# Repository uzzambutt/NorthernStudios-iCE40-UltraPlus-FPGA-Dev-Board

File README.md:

# NorthernStudios iCE40-UltraPlus FPGA Dev Board (V2)

<p align="center">
  <b>Designed by: Muhammad Uzzam Butt</b>
</p>

<p align="center">

</p>

---

## Overview
**NorthernStudios iCE40-UltraPlus FPGA Dev Board (V2)** is a small, open-source development board based on the tiny form factor that utilizes **Lattice iCE40 UltraPlus (iCE40UP5K)** FPGA. This development board is specially built for low power edge computing, TinyML, RISC-V softcores and hardware developments.

The features of this development board include the integrated USB-to-UART bridge, 128M-bit SPI Flash and the multi rail power supply system.

---

##  Hardware Specifications

### FPGA Chip: Lattice iCE40UP5K
* **Logic Cells**: 5,280 Look-Up Tables (LUTs)
* **Block RAM (BRAM)**: 120 Kbit
* **Single-Port RAM (SPRAM)**: 1,024 Kbit (128 KB, ideal for microcontroller program memory)
* **DSP Blocks**: 8 (16x16 multiplier + 32-bit accumulator)
* **Hardened IP**: 2x I2C, 2x SPI
* **Constant Current Drivers**: 3x 24mA dedicated driver outputs (suited for RGB LED control)

### Important components
| Component | Function | Description |
| :--- | :--- | :--- |
| **FPGA** | [Lattice iCE40UP5K-SG48ITR](https://www.latticesemi.com/Products/FPGAandCPLD/iCE40UltraPlus) | SG48 package, 48-pin QFN, highly integrated low-power FPGA. |
| **USB-to-UART Bridge** | [Silicon Labs CP2102N](https://www.silabs.com/interface/usb-bridges/usbtouart/device.cp2102n-a02-gqfn24) | High-speed USB-to-UART bridge for programming and serial debugging via USB-C. |
| **SPI Flash** | Winbond W25Q128JVS (128M-bit / 16MB) | Stores FPGA configuration bitstreams and extra user data or filesystem blocks. |
| **Reference Oscillator** | Seiko Epson SG-210STF (12 MHz) | Ultra-precise active crystal oscillator providing a stable system reference clock. |
| **Power Regulators** | Diodes Inc. AP2112K LDOs | Generates +1.2V (Core), +1.8V (PLL/VCC), +2.5V (Auxiliary), and +3.3V (I/O & Flash) from USB +5V. |
| **USB Connector** | USB Type-C Receptacle (14-Pin) | Handles 5V power supply, programming interface, and UART communications. |

---

##  Onboard Interfaces & I/O
* **RGB LED**: Dedicated addressable RGB LED (LED_ARGB) connected to the FPGA's constant current outputs for status and visualization.
* **User I/O**: Multi-pin expansion breakout headers featuring standard 0.1" pitch GPIO pins.
* **Tactile Buttons**:
  * Reset Button
  * User Programmable Button

---

## PCB Design & Layers

This PCB is designed as a high-density, **4-layer board** utilizing KiCad to ensure clean signal routing, stable ground planes, and dedicated power rails. 

###  Outer Silkscreen & Soldermask
* **Front View (Main Thumbnail)**:
  
* **Back View**:

###  Internal Copper Layers
* **Layer 1 (L1 - Top Copper / Signals)**:
  
* **Layer 2 (L2 - Inner Ground Plane)**:
  
* **Layer 3 (L3 - Inner Power Plane)**:
  
* **Layer 4 (L4 - Bottom Copper / Signals)**:

---

## Bill of Materials (BOM)

The complete bill of materials for the board is listed below. You can also view the raw CSV file [bom.csv](file:///D:/NS%20FPGA%20V2/NS%20FPGA%20V2%20iCE/jlcpcb/production_files/bom.csv).

| Comment | Designator | Footprint | LCSC | Quantity |
| :--- | :--- | :--- | :--- | :--- |
| 0.1uF | C10,C11,C14,C18,C19,C20,C21,C22,C23,C24,C26 | C_0402_1005Metric | C141382 | 11 |
| 1.5k | R12,R13,R14,R17 | R_0402_1005Metric | C25867 | 4 |
| 100 | R8 | R_0603_1608Metric | C22775 | 1 |
| 100nF | C15,C17 | C_0402_1005Metric | C1525 | 2 |
| 10k | R10,R11,R15,R16,R6,R7 | R_0402_1005Metric | C25531 | 6 |
| 10uF | C16 | C_0402_1005Metric | C15525 | 1 |
| 10uF | C1,C2,C3,C4,C5,C6,C7,C8 | C_0603_1608Metric | C19702 | 8 |
| 1k | R1 | R_0402_1005Metric | C25543 | 1 |
| 1uF | C25 | C_0402_1005Metric | C52923 | 1 |
| 22.1k | R5 | R_0402_1005Metric | C43473 | 1 |
| 4.7uF | C12,C13,C9 | C_0402_1005Metric | C23733 | 3 |
| 47.5k | R4 | R_0402_1005Metric | C137974 | 1 |
| 5.1k | R2,R3 | R_0603_1608Metric | C23186 | 2 |
| AP2112K-1.2 | U5 | SOT-23-5 | C460310 | 1 |
| AP2112K-1.8 | U7 | SOT-23-5 | C3021123 | 1 |
| AP2112K-2.5 | U6 | SOT-23-5 | C49451993 | 1 |
| AP2112K-3.3 | U4 | SOT-23-5 | C51118 | 1 |
| CP2102N-Axx-xQFN24 | U3 | QFN-24-1EP_4x4mm_P0.5mm_EP2.6x2.6mm | C969151 | 1 |
| D_Schottky | D1 | D_0603_1608Metric | C6770543 | 1 |
| ICE40UP5K-SG48ITR | U1 | QFN-48-1EP_7x7mm_P0.5mm_EP5.1x5.1mm | C2678152 | 1 |
| LED | D2,D4 | LED_0402_1005Metric | C130723 | 2 |
| LED_ARGB | D3 | LED_RGB_Wuerth-PLCC4_3.2x2.8mm_150141M173100 | C7288905 | 1 |
| R22 | R9 | R_0402_1005Metric | C25092 | 1 |
| SG-210STF | Y1 | Oscillator_SMD_SeikoEpson_SG210-4Pin_2.5x2.0mm | C728996 | 1 |
| SW_Push | SW1 | SW_Push_1P1T_NO_CK_KMR2 | C221679 | 1 |
| USB_C_Receptacle_USB2.0_14P | J1 | USB_C_Receptacle_HRO_TYPE-C-31-M-12 | C2894897 | 1 |
| W25Q128JVS | U2 | SOIC-8_5.3x5.3mm_P1.27mm | C97521 | 1 |
| Conn_02x03_Odd_Even | J5 | PinHeader_2x03_P1.00mm_Vertical | | 1 |
| Conn_02x03_Odd_Even | J4 | PinHeader_2x03_P1.00mm_Vertical | | 1 |
| TestPoint_Small | TP4 | TestPoint_Pad_D1.0mm | | 1 |
| TestPoint_Small | TP3 | TestPoint_Pad_D1.0mm | | 1 |
| TestPoint_Small | TP2 | TestPoint_Pad_D1.0mm | | 1 |
| TestPoint_Small | TP1 | TestPoint_Pad_D1.0mm | | 1 |
| Conn_01x07_Pin | J6 | PinHeader_1x07_P2.54mm_Vertical | | 1 |
| Conn_01x20_Pin | J3 | PinHeader_1x20_P2.54mm_Vertical | | 1 |
| Conn_01x20_Pin | J2 | PinHeader_1x20_P2.54mm_Vertical | | 1 |

---

## Getting Started

### 💻 Open Source Toolchain Setup
The Lattice iCE40 UltraPlus is fully supported by the open-source FPGA toolchain, providing quick compilation and programming:

1. **Synthesis**: [Yosys](https://github.com/YosysHQ/yosys)
2. **Place & Route**: [nextpnr](https://github.com/YosysHQ/nextpnr) (using target `--up5k`)
3. **Bitstream Packing**: [icepack](https://github.com/YosysHQ/icestorm)
4. **Programming**: [iceprog](https://github.com/YosysHQ/icestorm)

*Note: You can also use Lattice's IDE **Lattice Radiant** or **iCEcube2**.*

---

##  License

This project is licensed under the **MIT License**. For details, see the [LICENSE](LICENSE) file.

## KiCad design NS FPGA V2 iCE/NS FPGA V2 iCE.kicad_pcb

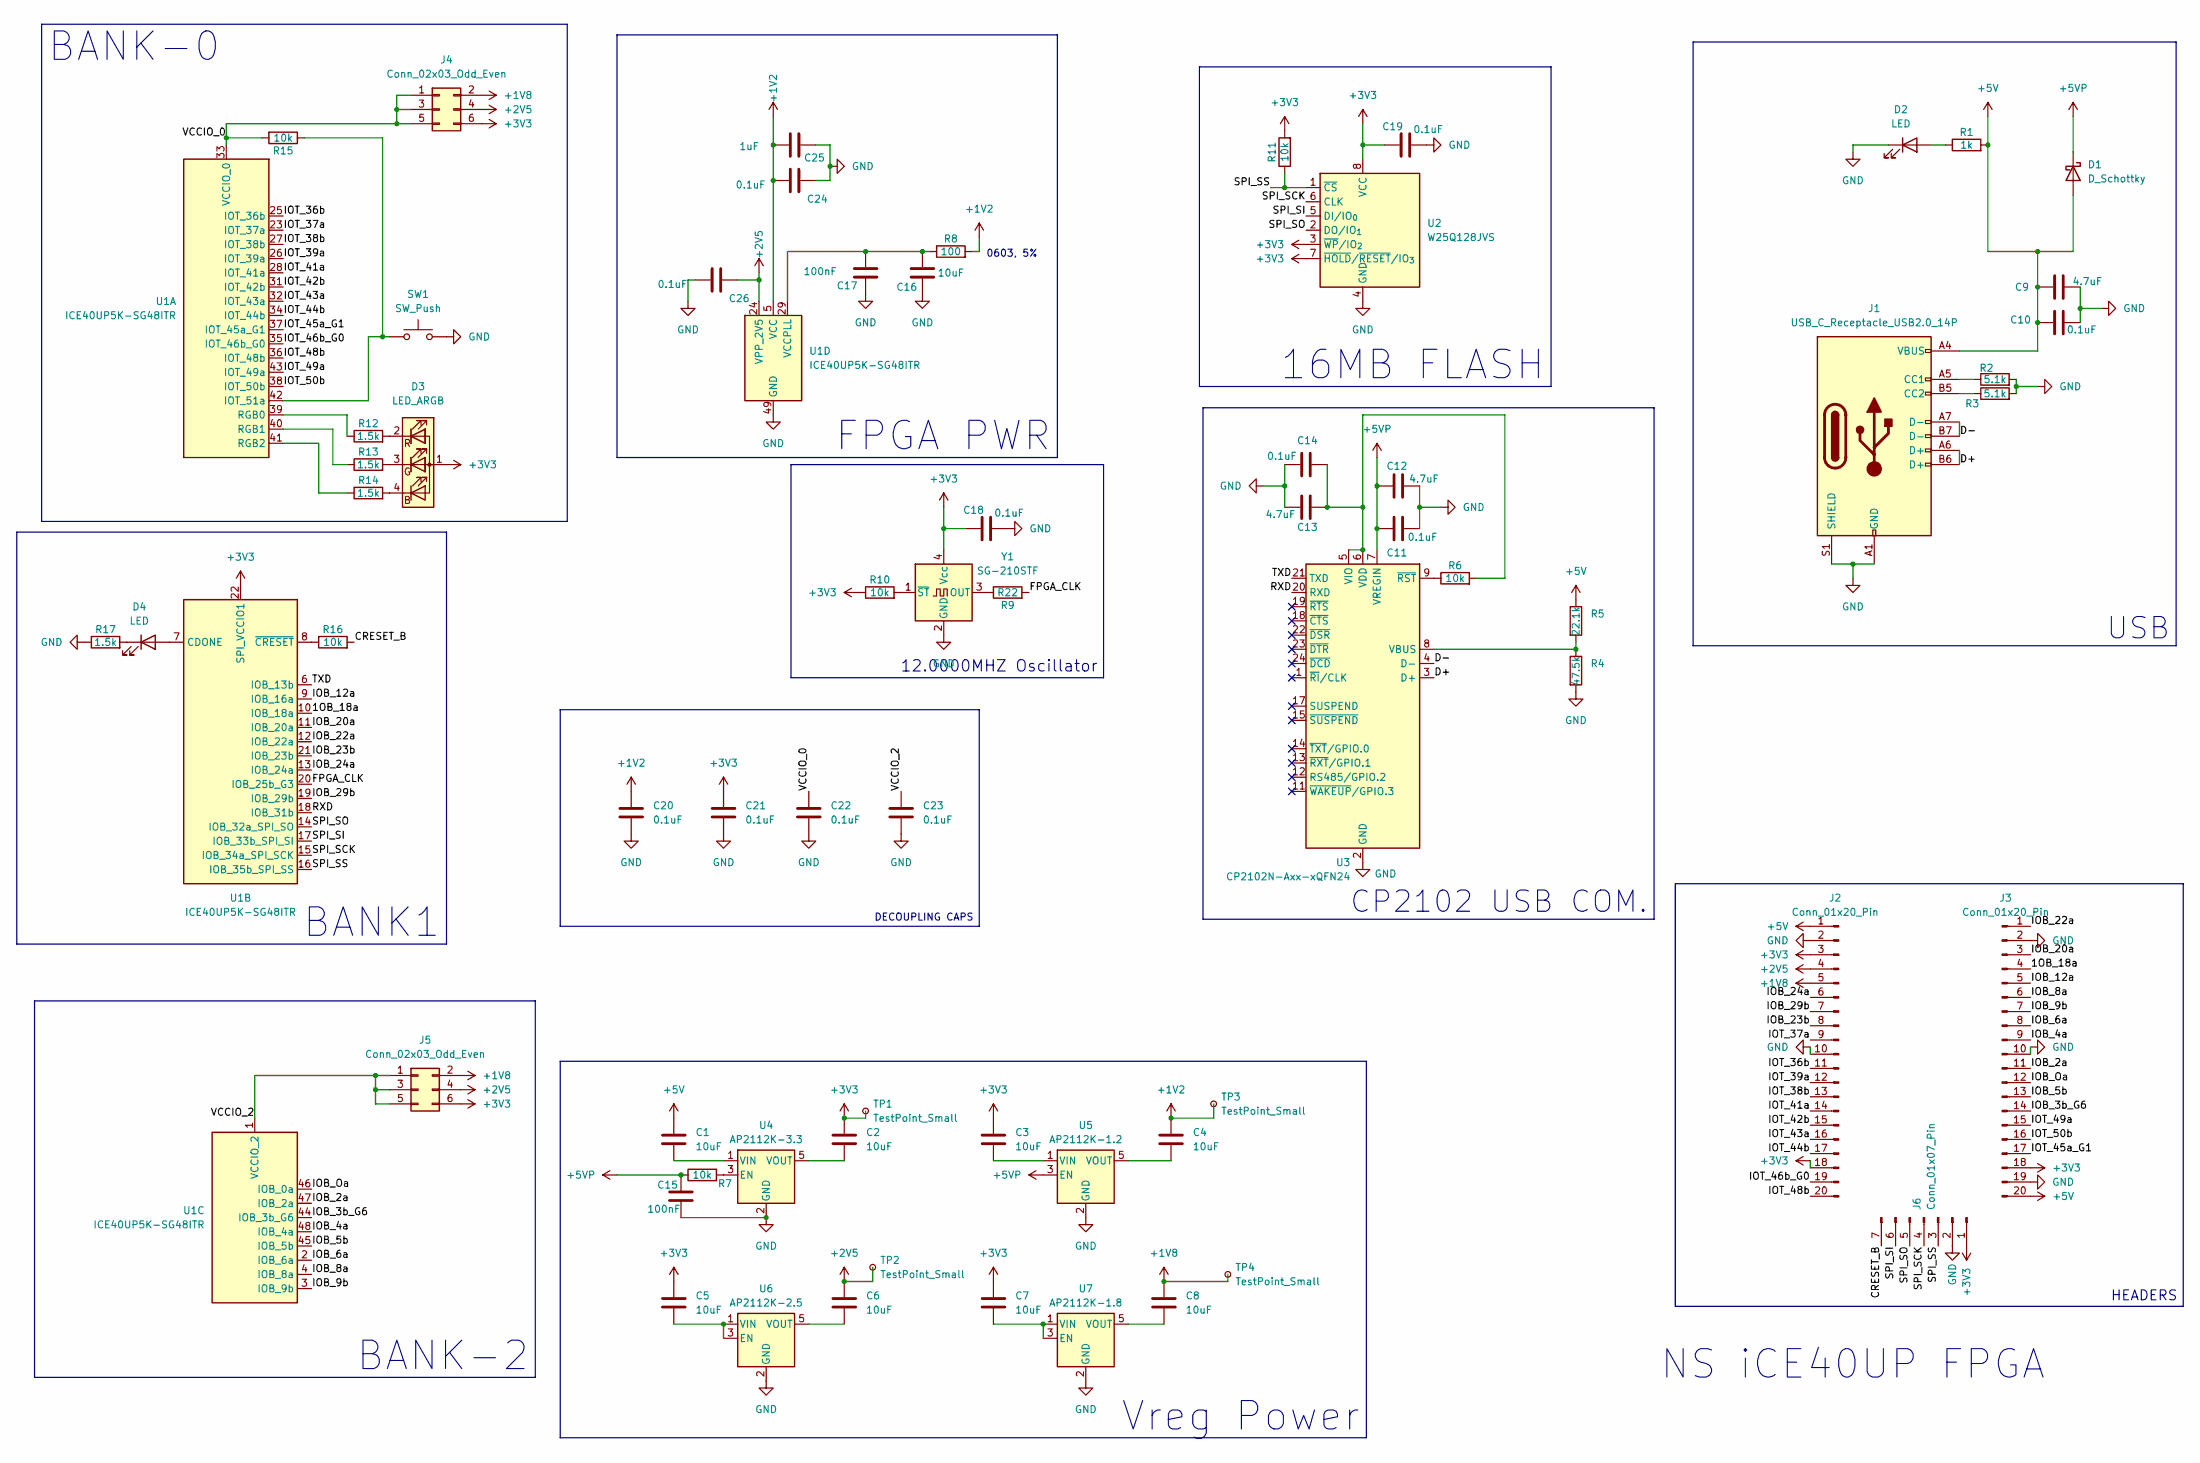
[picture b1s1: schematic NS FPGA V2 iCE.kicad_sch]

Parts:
C1, C2, C3, C4, C5, C6, C7, C8: 10uF; C_0603_1608Metric
C9, C12, C13: 4.7uF; C_0402_1005Metric
C10, C11, C14, C18, C19, C20, C21, C22, C23, C24, C26: 0.1uF; C_0402_1005Metric
C15, C17: 100nF; C_0402_1005Metric
C16: 10uF; C_0402_1005Metric
C25: 1uF; C_0402_1005Metric
D1: D_Schottky; D_0603_1608Metric
D2, D4: LED; LED_0402_1005Metric
D3: LED_ARGB; LED_RGB_Wuerth-PLCC4_3.2x2.8mm_150141M173100
J1: USB_C_Receptacle_USB2.0_14P; USB_C_Receptacle_HRO_TYPE-C-31-M-12
J2, J3: Conn_01x20_Pin; PinHeader_1x20_P2.54mm_Vertical
J4, J5: Conn_02x03_Odd_Even; PinHeader_2x03_P1.00mm_Vertical
J6: Conn_01x07_Pin; PinHeader_1x07_P2.54mm_Vertical
R1: 1k; R_0402_1005Metric
R2, R3: 5.1k; R_0603_1608Metric
R4: 47.5k; R_0402_1005Metric
R5: 22.1k; R_0402_1005Metric
R6, R7, R10, R11, R15, R16: 10k; R_0402_1005Metric
R8: 100; R_0603_1608Metric
R9: R22; R_0402_1005Metric
R12, R13, R14, R17: 1.5k; R_0402_1005Metric
SW1: SW_Push; SW_Push_1P1T_NO_CK_KMR2
TP1, TP2, TP3, TP4: TestPoint_Small; TestPoint_Pad_D1.0mm
U1: ICE40UP5K-SG48ITR; QFN-48-1EP_7x7mm_P0.5mm_EP5.1x5.1mm
U2: W25Q128JVS; SOIC-8_5.3x5.3mm_P1.27mm
U3: CP2102N-Axx-xQFN24; QFN-24-1EP_4x4mm_P0.5mm_EP2.6x2.6mm
U4: AP2112K-3.3; SOT-23-5
U5: AP2112K-1.2; SOT-23-5
U6: AP2112K-2.5; SOT-23-5
U7: AP2112K-1.8; SOT-23-5
Y1: SG-210STF; Oscillator_SMD_SeikoEpson_SG210-4Pin_2.5x2.0mm

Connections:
+1V2: C4.1, C20.1, C24.1, C25.1, R8.2, TP3.1, U1.5 (VCC), U1.30 (VCC)
+1V8: C8.1, J2.5, J4.2, J5.2, TP4.1
+2V5: C6.1, C26.2, J2.4, J4.4, J5.4, TP2.1, U1.24 (VPP_2V5)
+3V3: C2.1, C3.1, C5.1, C7.1, C18.2, C19.2, C21.1, D3.1 (A), J2.3, J2.18, J3.18, J4.6, J5.6, J6.1, R10.1, R11.2, TP1.1, U1.22 (SPI_VCCIO1), U2.3 (~WP/IO_{2}), U2.7 (~HOLD/~RESET/IO_{3}), U2.8 (VCC), Y1.4 (Vcc)
+5V: C1.1, C9.1, C10.1, D1.2 (A), J1.A4 (VBUS), J1.A9 (VBUS), J1.B4 (VBUS), J1.B9 (VBUS), J2.1, J3.20, R1.2, R5.1
+5VP: C11.1, C12.1, C15.2, D1.1 (K), R7.1, U3.7 (VREGIN), U5.3 (EN)
/1OB_18a: J3.4, U1.10 (IOB_18a)
/CRESET_B: J6.7, R16.2
/D+: J1.A6 (D+), J1.B6 (D+), U3.3 (D+)
/D-: J1.A7 (D-), J1.B7 (D-), U3.4 (D-)
/FPGA_CLK: R9.2, U1.20 (IOB_25b_G3)
/IOB_2a: J3.11, U1.47 (IOB_2a)
/IOB_3b_G6: J3.14, U1.44 (IOB_3b_G6)
/IOB_4a: J3.9, U1.48 (IOB_4a)
/IOB_5b: J3.13, U1.45 (IOB_5b)
/IOB_6a: J3.8, U1.2 (IOB_6a)
/IOB_8a: J3.6, U1.4 (IOB_8a)
/IOB_9b: J3.7, U1.3 (IOB_9b)
/IOB_12a: J3.5, U1.9 (IOB_16a)
/IOB_20a: J3.3, U1.11 (IOB_20a)
/IOB_22a: J3.1, U1.12 (IOB_22a)
/IOB_23b: J2.8, U1.21 (IOB_23b)
/IOB_24a: J2.6, U1.13 (IOB_24a)
/IOB_29b: J2.7, U1.19 (IOB_29b)
/IOB_Oa: J3.12, U1.46 (IOB_0a)
/IOT_36b: J2.11, U1.25 (IOT_36b)
/IOT_37a: J2.9, U1.23 (IOT_37a)
/IOT_38b: J2.13, U1.27 (IOT_38b)
/IOT_39a: J2.12, U1.26 (IOT_39a)
/IOT_41a: J2.14, U1.28 (IOT_41a)
/IOT_42b: J2.15, U1.31 (IOT_42b)
/IOT_43a: J2.16, U1.32 (IOT_43a)
/IOT_44b: J2.17, U1.34 (IOT_44b)
/IOT_45a_G1: J3.17, U1.37 (IOT_45a_G1)
/IOT_46b_G0: J2.19, U1.35 (IOT_46b_G0)
/IOT_48b: J2.20, U1.36 (IOT_48b)
/IOT_49a: J3.15, U1.43 (IOT_49a)
/IOT_50b: J3.16, U1.38 (IOT_50b)
/RXD: U1.18 (IOB_31b), U3.20 (RXD)
/SPI_SCK: J6.4, U1.15 (IOB_34a_SPI_SCK), U2.6 (CLK)
/SPI_SI: J6.6, U1.17 (IOB_33b_SPI_SI), U2.5 (DI/IO_{0})
/SPI_SO: J6.5, U1.14 (IOB_32a_SPI_SO), U2.2 (DO/IO_{1})
/SPI_SS: J6.3, R11.1, U1.16 (IOB_35b_SPI_SS), U2.1 (~CS)
/TXD: U1.6 (IOB_13b), U3.21 (TXD)
/VCCIO_0: C22.1, J4.1, J4.3, J4.5, R15.2, U1.33 (VCCIO_0)
/VCCIO_2: C23.1, J5.1, J5.3, J5.5, U1.1 (VCCIO_2)
GND: C9.2, C10.2, C11.2, C12.2, C13.2, C14.2, C15.1, C16.2, C17.2, C18.1, C19.1, C20.2, C21.2, C22.2, C23.2, C24.2, C25.2, C26.1, D2.1 (K), J1.A1 (GND), J1.A12 (GND), J1.B1 (GND), J1.B12 (GND), J1.S1 (SHIELD), J2.2, J2.10, J3.2, J3.10, J3.19, J6.2, R2.2, R3.2, R4.2, R17.1, SW1.2, U1.49 (GND), U2.4 (GND), U3.2 (GND), U3.25 (GND), U4.2 (GND), U5.2 (GND), U6.2 (GND), U7.2 (GND), Y1.2 (GND)
unnamed: D2.2 (A), R1.1
unnamed: D3.4 (BK), R14.2
unnamed: D3.3 (GK), R13.2
unnamed: D3.2 (RK), R12.2
unnamed: D4.2 (A), U1.7 (CDONE)
unnamed: D4.1 (K), R17.2
unnamed: J1.A5 (CC1), R2.1
unnamed: J1.B5 (CC2), R3.1
unnamed: R15.1, SW1.1, U1.42 (IOT_51a)
unnamed: R12.1, U1.39 (RGB0)
unnamed: R13.1, U1.40 (RGB1)
unnamed: R14.1, U1.41 (RGB2)
unnamed: R16.1, U1.8 (~CRESET)
unnamed: C16.1, C17.1, R8.1, U1.29 (VCCPLL)
unnamed: R4.1, R5.2, U3.8 (VBUS)
unnamed: C13.1, C14.1, R6.2, U3.5 (VIO), U3.6 (VDD)
unnamed: R6.1, U3.9 (~RST)
unnamed: R7.2, U4.3 (EN)
unnamed: C1.2, U4.1 (VIN)
unnamed: C2.2, U4.5 (VOUT)
unnamed: C3.2, U5.1 (VIN)
unnamed: C4.2, U5.5 (VOUT)
unnamed: C5.2, U6.1 (VIN), U6.3 (EN)
unnamed: C6.2, U6.5 (VOUT)
unnamed: C7.2, U7.1 (VIN), U7.3 (EN)
unnamed: C8.2, U7.5 (VOUT)
unnamed: R9.1, Y1.3 (OUT)
unnamed: R10.2, Y1.1 (~ST)

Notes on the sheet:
0603, 5%
NS iCE40UP FPGA
BANK-2
FPGA PWR
16MB FLASH
Vreg Power
USB
BANK1
CP2102 USB COM.
BANK-0
12.0000MHZ Oscillator
HEADERS
DECOUPLING CAPS

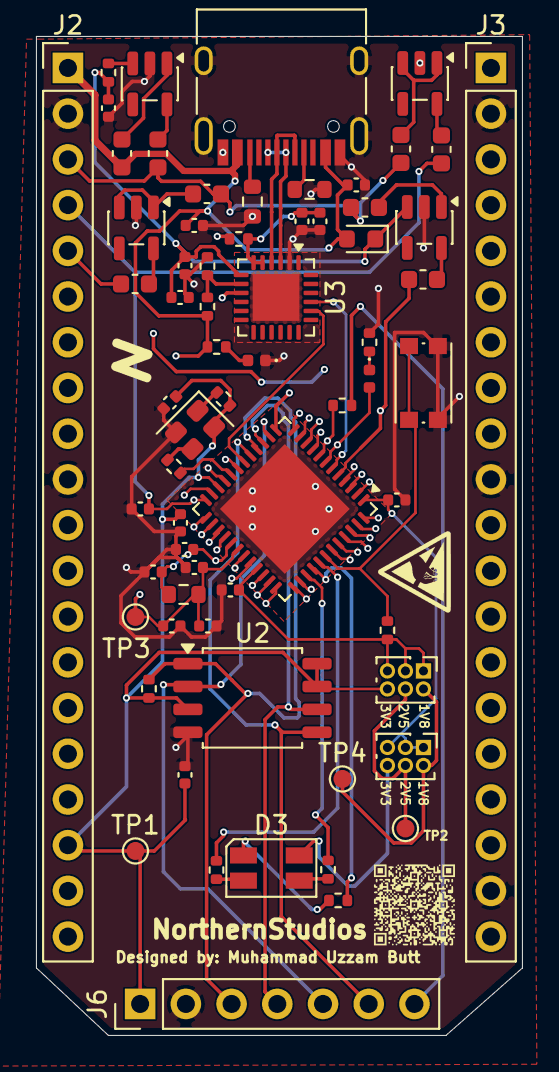
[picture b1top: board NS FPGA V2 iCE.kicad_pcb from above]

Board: 4 copper layers, 27.0 x 55.5 mm, 66 parts (0 on the bottom side), 75 nets.

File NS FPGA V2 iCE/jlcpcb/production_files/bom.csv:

Comment,Designator,Footprint,LCSC,Quantity
0.1uF,"C10,C11,C14,C18,C19,C20,C21,C22,C23,C24,C26",C_0402_1005Metric,C141382,11
1.5k,"R12,R13,R14,R17",R_0402_1005Metric,C25867,4
100,R8,R_0603_1608Metric,C22775,1
100nF,"C15,C17",C_0402_1005Metric,C1525,2
10k,"R10,R11,R15,R16,R6,R7",R_0402_1005Metric,C25531,6
10uF,C16,C_0402_1005Metric,C15525,1
10uF,"C1,C2,C3,C4,C5,C6,C7,C8",C_0603_1608Metric,C19702,8
1k,R1,R_0402_1005Metric,C25543,1
1uF,C25,C_0402_1005Metric,C52923,1
22.1k,R5,R_0402_1005Metric,C43473,1
4.7uF,"C12,C13,C9",C_0402_1005Metric,C23733,3
47.5k,R4,R_0402_1005Metric,C137974,1
5.1k,"R2,R3",R_0603_1608Metric,C23186,2
AP2112K-1.2,U5,SOT-23-5,C460310,1
AP2112K-1.8,U7,SOT-23-5,C3021123,1
AP2112K-2.5,U6,SOT-23-5,C49451993,1
AP2112K-3.3,U4,SOT-23-5,C51118,1
CP2102N-Axx-xQFN24,U3,QFN-24-1EP_4x4mm_P0.5mm_EP2.6x2.6mm,C969151,1
D_Schottky,D1,D_0603_1608Metric,C6770543,1
ICE40UP5K-SG48ITR,U1,QFN-48-1EP_7x7mm_P0.5mm_EP5.1x5.1mm,C2678152,1
LED,"D2,D4",LED_0402_1005Metric,C130723,2
LED_ARGB,D3,LED_RGB_Wuerth-PLCC4_3.2x2.8mm_150141M173100,C7288905,1
R22,R9,R_0402_1005Metric,C25092,1
SG-210STF,Y1,Oscillator_SMD_SeikoEpson_SG210-4Pin_2.5x2.0mm,C728996,1
SW_Push,SW1,SW_Push_1P1T_NO_CK_KMR2,C221679,1
USB_C_Receptacle_USB2.0_14P,J1,USB_C_Receptacle_HRO_TYPE-C-31-M-12,C2894897,1
W25Q128JVS,U2,SOIC-8_5.3x5.3mm_P1.27mm,C97521,1
Conn_02x03_Odd_Even,J5,PinHeader_2x03_P1.00mm_Vertical,,1
Conn_02x03_Odd_Even,J4,PinHeader_2x03_P1.00mm_Vertical,,1
TestPoint_Small,TP4,TestPoint_Pad_D1.0mm,,1
TestPoint_Small,TP3,TestPoint_Pad_D1.0mm,,1
TestPoint_Small,TP2,TestPoint_Pad_D1.0mm,,1
TestPoint_Small,TP1,TestPoint_Pad_D1.0mm,,1
Conn_01x07_Pin,J6,PinHeader_1x07_P2.54mm_Vertical,,1
Conn_01x20_Pin,J3,PinHeader_1x20_P2.54mm_Vertical,,1
Conn_01x20_Pin,J2,PinHeader_1x20_P2.54mm_Vertical,,1

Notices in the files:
README.md:
License: MIT
